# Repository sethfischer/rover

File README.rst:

=================
sethfischer/rover
=================

|build-status| |lint-status| |test-status| |docs-status| |linkcheck-status| |build-pcb-status|

Quarter-scale Mars rover based on the NASA Mars 2020 Mission Perseverance Rover.

Construction
------------

Refer to the `documentation <https://rover.fischer.nz/>`__.

Contribute
----------

Refer to `how to build a release`_ and follow the `additional steps for developers`_.

License
-------

:Software: SPDX-License-Identifier: MIT
:Hardware: SPDX-License-Identifier: CERN-OHL-W-2.0
:Documentation: SPDX-License-Identifier: CC-BY-NC-SA-4.0

.. _`how to build a release`: https://rover.fischer.nz/en/latest/build-release.html
.. _`additional steps for developers`: https://rover.fischer.nz/en/latest/build-release.html#additional-steps-for-developers

.. |build-status| image:: https://github.com/sethfischer/rover/actions/workflows/build.yml/badge.svg
    :target: https://github.com/sethfischer/rover/actions/workflows/build.yml
    :alt: Build status
.. |lint-status| image:: https://github.com/sethfischer/rover/actions/workflows/lint.yml/badge.svg
    :target: https://github.com/sethfischer/rover/actions/workflows/lint.yml
    :alt: Lint status
.. |test-status| image:: https://github.com/sethfischer/rover/actions/workflows/test.yml/badge.svg
    :target: https://github.com/sethfischer/rover/actions/workflows/test.yml
    :alt: Test status
.. |docs-status| image:: https://readthedocs.org/projects/sethfischer-osr/badge/?version=latest
    :target: https://sethfischer-osr.readthedocs.io/en/latest/?badge=latest
    :alt: Documentation Status
.. |linkcheck-status| image:: https://github.com/sethfischer/rover/actions/workflows/linkcheck.yml/badge.svg
    :target: https://github.com/sethfischer/rover/actions/workflows/linkcheck.yml
    :alt: Link Check Status
.. |build-pcb-status| image:: https://github.com/sethfischer/rover/actions/workflows/build-pcb.yml/badge.svg
    :target: https://github.com/sethfischer/rover/actions/workflows/build-pcb.yml
    :alt: PCB build status

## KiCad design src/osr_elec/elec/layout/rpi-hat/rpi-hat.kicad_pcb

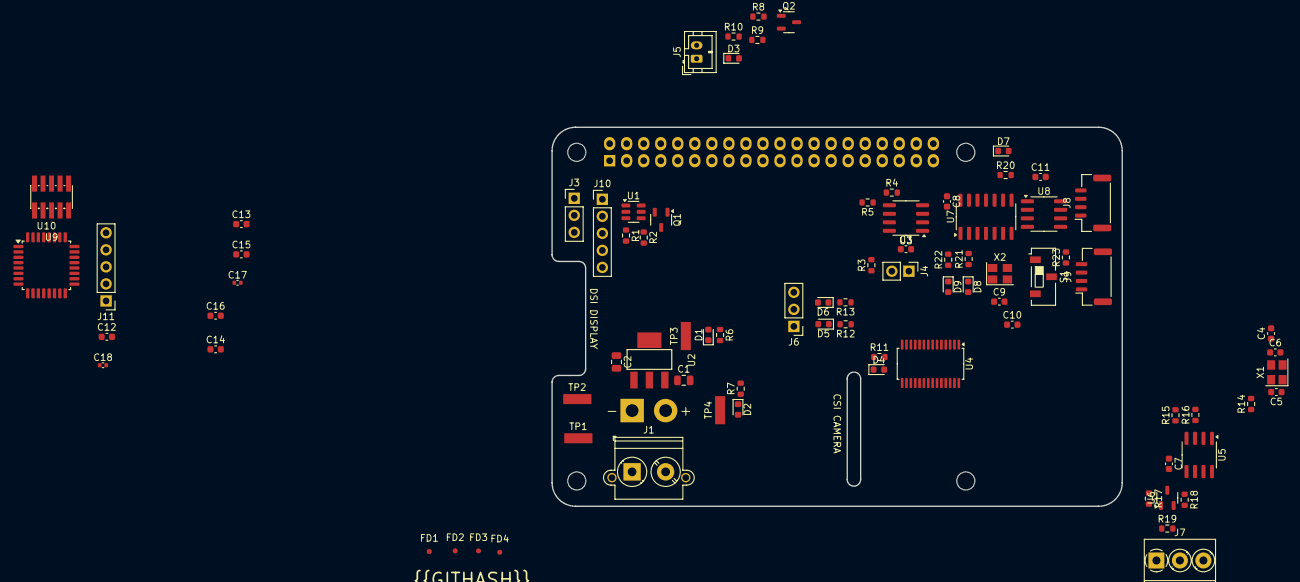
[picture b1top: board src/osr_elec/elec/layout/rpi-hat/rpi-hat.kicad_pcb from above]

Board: 4 copper layers, 85.0 x 56.5 mm, 88 parts (1 on the bottom side), 65 nets, no tracks yet.

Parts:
C1, C2: 25V 10uF X5R ±10% 0805 Multilayer Ceramic Capacit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; C0805
C3, C4, C7, C8, C11, C12, C13, C15: 50V 100nF X7R ±10% 0603 Multilayer Ceramic Capaci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; C0603
C5, C6, C9, C10: ?; C0603
C14, C16: 16V 4.7uF X5R ±10% 0603 Multilayer Ceramic Capaci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; C0603
C17: 50V 10nF X7R ±10% 0402 Multilayer Ceramic Capacit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; C0402
C18: 25V 1uF X5R ±10% 0402 Multilayer Ceramic Capacito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; C0402
D1, D2, D3, D4, D5, D6, D7, D8, D9: ?; LED_0603_1608Metric
FD1, FD2, FD3, FD4: ?; Fiducial_0.75mm_Mask1.5mm
J1: ?; Combo__AMASS_XT30PW-M_1x02_P2.50mm_Horizontal__TerminalBloc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
J2: ?; PinSocket_Samtec_ESQ-120-23-T-D_Oval_Pads
J3, J6: ?; PinHeader_1x03_P2.54mm_Vertical
J4: ?; PinHeader_1x02_P2.54mm_Vertical
J5: ?; JST_PH_B2B-PH-K_1x02_P2.00mm_Vertical
J7: ?; TerminalBlock_Phoenix_PT-1,5-3-3.5-H_1x03_P3.50mm_Horizontal
J8, J9: ?; JST_GH_SM04B-GHS-TB_1x04-1MP_P1.25mm_Horizontal
J10, J11: ?; PinHeader_1x05_P2.54mm_Vertical
Q1, Q2: ?; SOT-23-3
R1, R16: 100mW Thick Film Resistors 75V ±100ppm/℃ ±1% 10kΩ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; R0603
R2: 100mW Thick Film Resistors 75V ±100ppm/℃ ±1% 47kΩ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; R0603
R3: 100mW Thick Film Resistors 75V ±100ppm/℃ ±1% 1kΩ 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; R0603
R4, R5: 100mW Thick Film Resistors 75V ±100ppm/℃ ±1% 3.3k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; R0603
R6: 100mW Thick Film Resistors 75V ±100ppm/℃ ±1% 226Ω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; R0603
R7: 100mW Thick Film Resistors ±100ppm/℃ ±1% 487Ω 060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; R0603
R8: 100mW Thick Film Resistors 75V ±1% ±200ppm/℃ 100Ω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; R0603
R9: 100mW Thick Film Resistors 75V ±100ppm/℃ ±1% 1MΩ 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; R0603
R10: 100mW Thick Film Resistors 75V ±100ppm/℃ ±1% 402Ω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; R0603
R11, R20: 100mW Thin Film Resistor 75V ±25ppm/℃ ±0.1% 84.5Ω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; R0603
R12, R21: 100mW Thick Film Resistors 75V ±100ppm/℃ ±1% 330Ω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; R0603
R13, R22: 166.667mW Thin Film Resistor 75V ±0.5% ±25ppm/℃ 3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; R0603
R14, R15: 100mW Thick Film Resistors 75V ±100ppm/℃ ±1% 20Ω 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; R0603
R17, R18: 100mW Thick Film Resistors 75V ±1% ±400ppm/℃ 10Ω 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; R0603
R19, R23: 100mW Thick Film Resistors 75V ±100ppm/℃ ±1% 120Ω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; R0603
S1: ?; CK_JS102011JCQN_SW_SPDT_Slide_SMD
TP1, TP2, TP3, TP4: ?; Koa_Speer_RCWCTE_test_point
U1: ?; SOT-23-6
U2: ?; SOT-223-3_L6.5-W3.4-P2.30-LS7.0-BR
U3, U5, U8: ?; SOIC-8_3.9x4.9mm_P1.27mm
U4: ?; TSSOP-28_4.4x9.7mm_P0.65mm
U6: ?; SOT-23-3
U7: ?; SOIC-14_3.9x8.7mm_P1.27mm
U9: ?; HDR-SMD_10P-P1.27-V-M-R2-C5-LS5.3
U10: ?; LQFP-32_7x7mm_P0.8mm
X1, X2: ?; Crystal_SMD_Abracon_ABM8G-4Pin_3.2x2.5mm
_MH1, _MH2, _MH3, _MH4: MountingHole_2.7mm_M2.5_DIN965

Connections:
can_con_trx.can_leds.led_rx.resistor-cathode: D9.1, R22.1
can_con_trx.can_leds.led_tx.resistor-cathode: D8.1, R21.1
can_con_trx.controller-io: D7.2, U7.9
can_con_trx.controller-rx: R21.2, U7.2, U8.4
can_con_trx.controller-tx: R22.2, U7.1, U8.1
can_con_trx.controller-xin: C9.1, U7.6, X2.1
can_con_trx.controller-xout: C10.1, U7.5, X2.3
can_con_trx.switch-p1: R23.1, S1.1
can_con_trx.user_led_indicator.resistor-cathode: D7.1, R20.1
canh: J8.2, J9.2, S1.2, U8.7
canl: J8.3, J9.3, R23.2, U8.6
di: R15.1, U5.4
dsr_b: D4.2, U4.18
gate: Q2.1, R8.2, R9.1
gnd: C1.2, C2.2, C3.2, C4.2, C7.2, C8.2, C9.2, C10.2, C11.2, C12.2, C13.2, C14.2, C15.2, C16.2, C17.2, C18.2, J1.1, J2.6, J2.9, J2.14, J2.20, J2.25, J2.30, J2.34, J2.39, J3.1, J4.1, J6.1, J7.3, J8.4, J8.MP, J9.4, J9.MP, J10.1, Q2.2, R1.2, R2.2, R6.2, R7.2, R9.2, R11.2, R12.2, R13.2, R16.2, R20.2, TP1.1, TP2.1, U2.1, U3.1, U3.2, U3.3, U3.4, U4.9, U4.22, U5.5, U6.3, U7.7, U8.2, U9.3, U9.5, U9.9, U10.16, U10.31, U10.32, X2.2, X2.4
id_eeprom.wp_pullup-p1: J4.2, R3.1
ideal_diode-vcc: J2.2, J2.4, Q1.2, U1.5
mcu.jtag_header-reset: C12.1, U9.10, U10.4
miso: J2.35, U4.12, U7.12
mosi: J2.38, U4.11, U7.11
output_enable: R16.1, U5.2, U5.3
pa8: J11.1, U10.18
pa9: J11.2, U10.19
pa10: J11.3, U10.20
pa11: J11.4, U10.21
pa12: J11.5, U10.22
power_indicator_3v3.resistor-cathode: D1.1, R6.1
power_indicator_5v.resistor-cathode: D2.1, R7.1
q1_base: R1.1, U1.1, U1.2, U1.3
q2_collector: Q1.1, R2.1, U1.4
ro: R14.1, U5.1
robot_signal_light.status_indicator.resistor-cathode: D3.1, R10.1
robot_signal_light.switch.fet-gnd: J5.2, Q2.3, R10.2
rpi_header.connector-cs: J2.12, U4.10
rpi_header.connector-cs-1: J2.36, U7.13
rpi_header.connector-io: J2.7, J10.2
rpi_header.connector-io-1: J2.11, R8.1
rpi_header.connector-io-2: J2.26, U7.4
rpi_header.connector-rx: J2.10, J3.3
rpi_header.connector-scl: J2.3, J10.3, U10.29
rpi_header.connector-scl-1: J2.28, R5.1, U3.6
rpi_header.connector-sda: J2.5, J10.4, U10.30
rpi_header.connector-sda-1: J2.27, R4.1, U3.5
rpi_header.connector-tx: J2.8, J3.2
rpi_header.connector-vcc: J2.1, J2.17
rs485_trx.series_resistors-a: J7.1, R17.2, R19.1, U6.1
rs485_trx.series_resistors-b: J7.2, R18.2, R19.2, U6.2
rs485_trx.trx-a: R17.1, U5.6
rs485_trx.trx-b: R18.1, U5.7
sck: J2.40, U4.13, U7.10
tck: U9.4, U10.24
tms: U9.2, U10.23
uart_converter-rx: D6.2, J6.3, U4.4
uart_converter-rx-1: R14.2, U4.24
uart_converter-tx: D5.2, J6.2, U4.3
uart_converter-tx-1: R15.2, U4.23
uart_converter.converter-xin: C5.1, U4.6, X1.1
uart_converter.converter-xout: C6.1, U4.7, X1.3
uart_converter.converter_osc-gnd: C5.2, C6.2, X1.2, X1.4
uart_converter.user_led_indicator.resistor-cathode: D4.1, R11.1
uart_leds.led_rx.resistor-cathode: D6.1, R13.1
uart_leds.led_tx.resistor-cathode: D5.1, R12.1
vcc-3v3: C2.1, C3.1, C4.1, C7.1, C8.1, C11.1, C13.1, C14.1, C15.1, C16.1, C17.1, C18.1, D1.2, D8.2, D9.2, J8.1, J9.1, J10.5, R4.2, R5.2, TP3.1, U2.2, U2.4, U3.8, U4.8, U5.8, U7.14, U8.3, U9.1, U10.1, U10.5, U10.17
vcc-5v: C1.1, D2.2, D3.2, J1.2, J5.1, Q1.3, TP4.1, U1.6, U2.3
wp: R3.2, U3.7

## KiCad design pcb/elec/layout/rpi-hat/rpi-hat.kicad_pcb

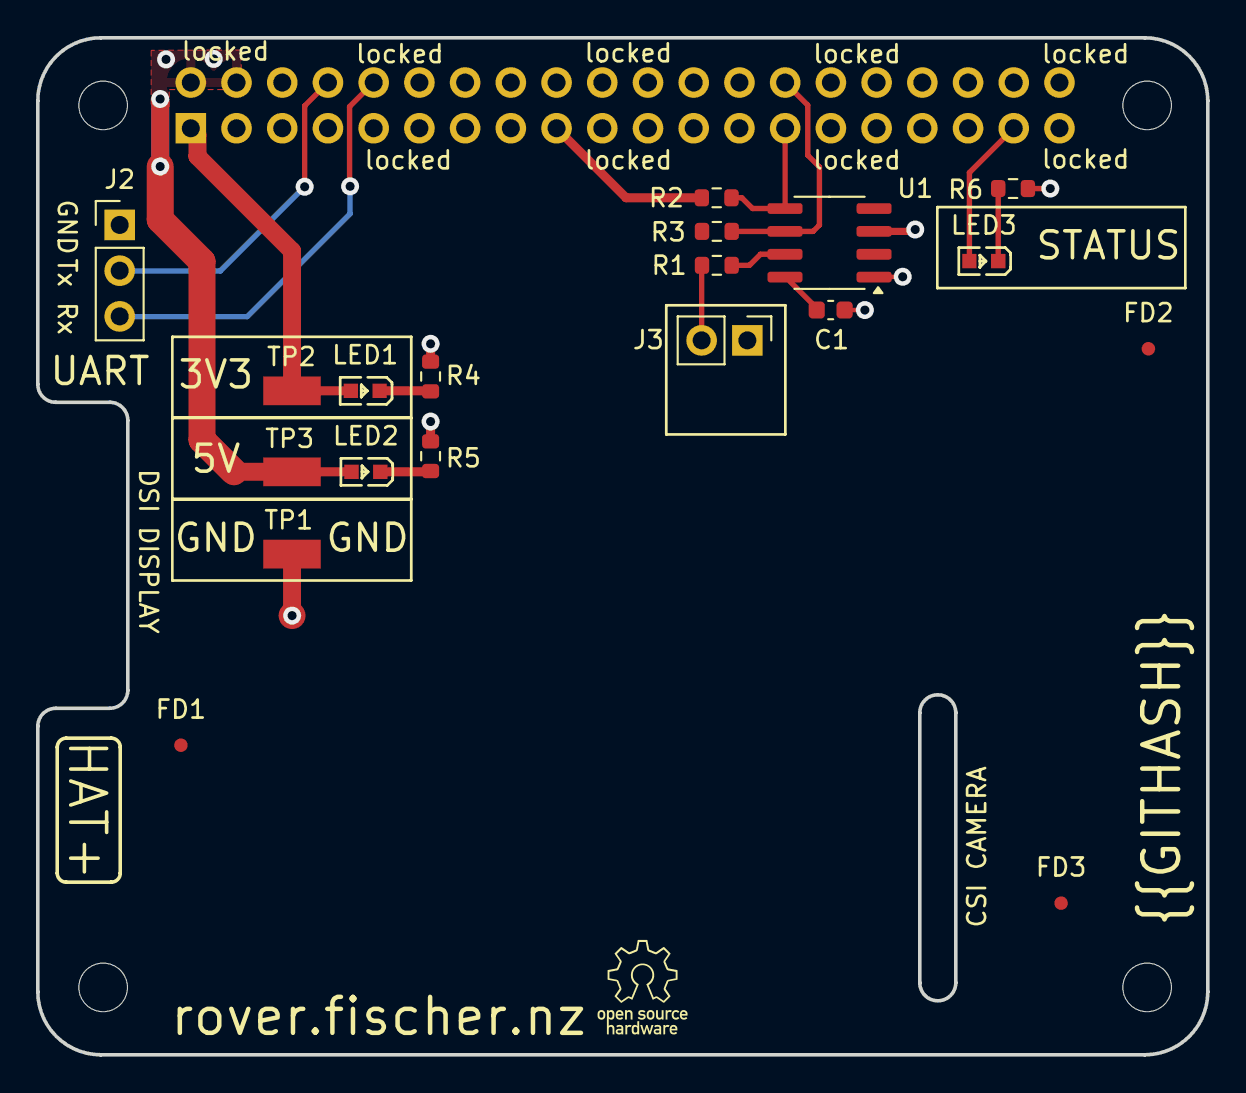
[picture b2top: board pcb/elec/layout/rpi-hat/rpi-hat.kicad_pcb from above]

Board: 2 copper layers, 65.0 x 56.5 mm, 26 parts (1 on the bottom side), 13 nets.

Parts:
C1: 50V 100nF X7R ±10% 0603 Multilayer Ceramic Capaci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; C0603
FD1, FD2, FD3: Fiducial_0.75mm_Mask1.5mm
GL1: Logo_RPi_Hat_Plus_Wordmark_3.5mm_SilkscreenTop
GL2: Logo_OSHW_5mm_SilkscreenTop
J1: PinSocket_2x20_P2.54mm_Vertical
J2: PinHeader_1x03_P2.54mm_Vertical
J3: PinHeader_1x02_P2.54mm_Vertical
LED1, LED2, LED3: LED0603-RD
R1: 100mW Thick Film Resistors 75V ±100ppm/℃ ±1% 1kΩ 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; R0603
R2, R3: 100mW Thick Film Resistors ±100ppm/℃ ±1% 3.9kΩ 06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; R0603
R4: 100mW Thick Film Resistors ±100ppm/℃ ±1% 226Ω 060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; R0603
R5: 100mW Thick Film Resistors ±100ppm/℃ ±1% 487Ω 060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; R0603
R6: 100mW Thin Film Resistor ±25ppm/℃ ±1% 549Ω 0603 C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; R0603
TP1, TP2, TP3: Koa_Speer_RCWCTE_test_point
U1: SOIC-8_3.9x4.9mm_P1.27mm
_MH1, _MH2, _MH3, _MH4: MountingHole_2.7mm

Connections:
gnd: C1.2, J1.6, J1.9, J1.14, J1.20, J1.25, J1.30, J1.34, J1.39, J2.1, J3.1, R4.2, R5.2, R6.2, TP1.1, U1.1, U1.2, U1.3, U1.4
gpio26: J1.37, LED3.2
p1: J3.2, R1.1
power_indicator_3v3.resistor-cathode: LED1.1, R4.1
power_indicator_5v.resistor-cathode: LED2.1, R5.1
rpi_header-scl-1: J1.28, R3.1, U1.6
rpi_header-sda-1: J1.27, R2.1, U1.5
rx: J1.10, J2.3
status_indicator_robot.resistor-cathode: LED3.1, R6.1
tx: J1.8, J2.2
vcc: C1.1, J1.1, J1.17, LED1.2, R2.2, R3.2, TP2.1, U1.8
vcc-1: J1.2, J1.4, LED2.2, TP3.1
wp: R1.2, U1.7

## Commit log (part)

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2022-09-04 build: update docs requirements
    Update due to change in format introduced by Poetry 1.2.0.
2022-09-05 feat: frame assembly
2022-09-06 refactor: implement class point2d
2022-09-06 refactor: read point2d values by name
2022-09-07 refactor: correctly reference class constants
2022-09-08 refactor: implement cq abstract base classes
2022-09-11 test: frame assembly and jigs
2022-09-11 test: aec 20 series v-slot extrusion
2022-09-11 test: aec 20-series bore slot sketch
2022-09-17 feat: rocker axle assembly
2022-09-18 build: update dependencies
2022-09-22 feat: export image of final assembly
2022-09-25 build: command to create open graph image
2022-09-25 build: update key words
2022-09-25 refactor: consistent naming
2022-09-25 refactor: consistent variable names
2022-09-26 docs: how to build a release
2022-09-26 build: include changelog in release
2022-09-26 fix: create venv with correct python version
2022-09-26 refactor: improve structure
2022-09-27 build: create release readme file
2022-09-27 docs: improved headings
2022-09-27 refactor: use config in open graph svg
2022-09-28 refactor: move long description to config
2022-09-28 fix: readme links
2022-09-28 refactor: move copyright notice to config
2022-09-28 build: poetry group cq-editor
2022-09-29 build: upgrade cq_warehouse
2022-09-30 build: create release archives
2022-10-01 refactor: replace invoke with subprocess
2022-10-01 refactor: import only used elements
2022-10-01 build: remove invoke mypy overrides
2022-10-09 feat: control electronics din rail and rpi
2022-10-09 refactor: mark make methods for internal use
2022-10-09 refactor: namespace assembly names
2022-10-09 build: fix out-of-date final assembly image
2022-10-09 build: optimise open graph image
2022-10-09 build: optimise exported png image
2022-10-09 docs: install optipng
2022-10-10 refactor: fix shadow of built-in name
2022-10-11 refactor: 2020 end tap jig
2022-10-11 build: use built-in collection types
2022-10-14 refactor: open graph card templates
2022-10-15 refactor: use cairosvg to render open graph card
2022-10-15 docs: improved parameter description
2022-10-15 test: alexco 2020 profile
2022-10-24 refactor: rocker axle assembly
2022-10-30 refactor: subclass control electronics
2022-11-04 feat: generate bill of materials
2022-11-05 build: git-lfs with rtd build process
2022-11-05 refactor: build release
2022-11-05 refactor: frame assembly names
2022-11-05 refactor: frame bom parts
2022-11-18 refactor: frame sub-assemblies
2022-11-18 refactor: remove call to deprecated method
2022-11-19 refactor: parts method name
2022-11-19 refactor: decouple base classes
2022-11-19 build: improve typing coverage
2022-11-20 refactor: rename post -> pillar
2022-11-20 fix: rocker axle location
2022-11-22 refactor: cq base classes
2022-11-23 refactor: generate assembly names
2022-11-23 refactor: rename axle_support -> axle_pillar
2022-11-26 fix: remove stdout info generated by export
2022-12-01 refactor: improve typing coverage
2022-12-01 refactor: export wrapper exception on stderr
2022-12-02 refactor: improve part identifier class
2022-12-02 refactor: store part quantity by assembly
2022-12-03 build: update pytest to 7.2.0
2022-12-03 build: update mypy to 0.991
2022-12-03 build: update sphinx to 5.3.0
2022-12-03 build: update dev dependencies
2022-12-03 docs: spelling corrections
2022-12-03 build: update git-lfs to 3.3.0
2022-12-06 build: update cadquery to 2.2.0b2
2022-12-08 build: remove poetry-core version
2022-12-08 build: consistent docstrings
2022-12-09 ci: fix workflow job name
2022-12-09 docs: bill of materials
2022-12-10 refactor: del unused variables
2022-12-10 refactor: correct variable names
2022-12-10 style: white-space changes
2022-12-10 build: spelling correction
2022-12-11 style: remove white-space in inline tables
2022-12-13 style: remove unused namespace from svg
2022-12-13 refactor: remove parameter used for solely test
2022-12-14 refactor: move common utilities into own package
2022-12-14 test: refactor v-slot tests
2022-12-14 test: refactor to use cq public api
2022-12-14 test: stricter type detection
2022-12-14 test: fix shf8 shaft support test
2022-12-15 refactor: stricter typing for cq containers
2022-12-15 ci: enable mypy strict mode
2022-12-16 build: type profile as cq sketch
2022-12-17 refactor: simple is keyword-only argument
2022-12-17 refactor: make cq export wrapper callable
2022-12-17 refactor: make fastener to part converter callable
2023-01-04 docs: bump copyright year
2023-01-10 docs: vtk render of main assembly and end-tap jig
2023-01-15 ci: upgrade github actions versions
2023-01-15 build: editor trim trailing whitespace
2023-01-15 style: format pyproject.toml
2023-01-15 build: install rtd dependencies with poetry
2023-01-21 build: update sphinxcontrib-cadquery to 0.3.0
2023-01-22 docs: refactor outline
2023-01-22 docs: add index entries
2023-01-22 docs: render frame assembly
2023-01-22 docs: show headings in toctree
2023-01-22 docs: add indices to side navigation
2023-01-22 docs: 3d print settings directive
2023-01-22 docs: 2020 end tap jig bom
2023-01-23 docs: render 2020 end-tap jig body
2023-01-23 docs: render frame sides
2023-01-24 docs: frame side boms
2023-01-25 refactor: osr sphinx domain
2023-01-29 build: update sphinxcontrib-cadquery to 0.4.0
2023-02-03 build: validate print settings nozzle, layer
2023-02-04 build: update cadquery to 2.2.0
2023-02-04 build: update cq-electronics
2023-02-04 build: add py.typed to osr_common module
2023-02-06 build: multilayer dxf builder utility
2023-02-06 refactor: move multilayer dxf class to osr_common
2023-02-06 refactor: move cq_wrappers to osr_common
2023-02-06 refactor: rename dxf exporter
2023-02-06 build: add metadata parameter to dxf exporter
2023-02-06 refactor: dxf exporter metadata default
2023-02-08 refactor: add param setup to dxf builder
2023-02-11 refactor: dxf exporter
    * init params to match ezdxf
    * imporved typing
    * improve doc strings
2023-02-14 docs: inspiration section
2023-02-16 docs: add dimensions calculated from model
2023-02-17 docs: fix perseverance model width on mobile
2023-02-17 docs: hide toc and add indices section
2023-02-24 docs: competitions section
2023-03-03 build: poetry disable modern installation
    Disable modern Poetry installation due to:
    AssertionError
    In cadquery_ocp-7.7.0a0-cp39-cp39-manylinux_2_31_x86_64.whl,
    LICENSES_bundled.txt is not mentioned in RECORD
    Modern installation was introduced with Poetry 1.4.0
2023-03-03 docs: fix dimension order
2023-03-05 build: update sphinxcontrib-cadquery to 0.5.0
2023-03-05 docs: add arc and iprc to competitions section
2023-03-25 docs: end-tap jig print orientation
2023-04-07 docs: tech promotion grid
2023-04-08 docs: link to github repo in header
2023-04-08 docs: frame sub assembly toc heading
2023-04-08 docs: add target for technology section
2023-04-09 docs: din rail assemblies
2023-04-09 docs: rocker axle section
2023-04-09 chore: remove duplicate conf variable
2023-04-10 chore: change project name to "sethfischer-rover"
2023-04-10 docs: add exiftool to build prerequisites
2023-04-21 docs: site icon
2023-04-22 docs: add sections copyright and about
2023-05-12 docs: update project description
2023-05-15 docs: add open graph image
2023-05-15 docs: improve meta descriptions
2023-05-16 docs: improve html page title
2023-05-16 docs: update index page title
2023-05-16 docs: update build release instructions
2023-05-17 chore: update dependencies
2023-05-17 chore: update mypy to 1.3.0
2023-05-17 chore: update cairosvg to 2.7.0
2023-05-26 docs: add lego technic rover to related projects
2023-06-28 docs: add captions to figures
2023-10-24 chore: bump pillow 9.5.0 -> 10.1.0
2023-10-24 chore: bump sphinx-design 0.4.1 -> 0.5.0
2023-12-01 docs: add geek club rover to related projects
2023-12-02 docs: update nasa-jpl website url
2023-12-02 test: periodic link check
2023-12-02 docs: update git-lfs url
2023-12-02 test: fix linkcheck workflow
2023-12-03 docs: remove sphero littlebits from related projects
    The Sphero LittleBits Space Rover Inventor Kit has been discontinued.
2023-12-05 test: configure linkcheck_allowed_redirects
2024-01-10 docs: link to documentation site
2024-01-10 chore: configure flake8-bugbear
2024-02-15 chore: bump cadquery 2.3.1 -> 2.4.0
2024-02-16 docs: generate changelog
2024-02-16 chore: set mwg image tags
2024-02-17 chore: require python 3.11
2024-02-17 refactor: make open graph card
2024-02-17 style: ignore pylint message w0212
2024-02-17 style: consistent single quotes
2024-02-19 style: prefix unused variable with underscore
2024-02-20 style: remove unused future imports
2024-02-21 refactor: point2d namedtuple
2024-02-22 ci: upgrade github actions/checkout 3 -> 4
2024-02-23 chore: fix cq-editor dependency resolution
2024-02-23 chore: downgrade pyqtgraph to ^0.12.4
2024-02-29 build: fix rtd build for poetry 1.8
2024-02-29 feat: command to generate rpi hat outline
2024-03-05 fix: rpi hat pcb outline
    Export only the face of the board as DXF.
2024-03-11 fix: exclude mounting holes from rpi hat outline
2024-03-11 fix: rpi pcb outline fillet
2024-03-25 feat: rpi hat pcb
2024-04-19 build: pinout sphinx extension
2024-04-19 docs: vmc pinout diagram
2024-06-11 docs: remove nasa-jpl 3d model
2024-06-17 docs: vmc daughter board directed graph
2024-06-21 feat: vmc daughter pcb
    Vehicle Management Computer daughter PCB.
2024-06-21 refactor: pin header 1x2 from headers package
2024-06-21 refactor: pin header 1x3 from headers package
2024-06-21 refactor: pin header 1x5 from headers package
2024-06-21 refactor: rpi gpoi header footprint from headers package
2024-06-21 chore: remove unused 3d model pin header 2x20
2024-06-21 refactor: rename can termination switch 3d model
2024-06-22 chore: update footprints
2024-06-23 refactor: can termination switch from ck-js-series package
2024-06-27 refactor: terminal block from package phoenix-pt-series
2024-06-28 chore: update footprint lib descriptions
2024-06-28 chore: remove pcb mech/ directory
2024-07-02 refactor: use kicad global libs for terminal block
2024-07-02 fix: remove make mech files
2024-07-10 chore: update black 24.2.0 -> 24.4.2
2024-07-10 chore: update mypy 1.8.0 -> 1.10.1
2024-07-10 chore: update pillow 10.2.0 -> 10.4.0
2024-07-11 chore: update dependencies
    Update dependencies:
    * certifi (2024.2.2 -> 2024.7.4)
    * idna (3.6 -> 3.7)
    * typing-extensions (4.9.0 -> 4.12.2)
    * urllib3 (2.2.1 -> 2.2.2)
    * annotated-types (0.6.0 -> 0.7.0)
2024-07-11 docs: update perseverance links
2024-07-11 docs: rename section vmc interfaces -> datasheet
2024-07-12 style: white space correction
2024-07-14 feat: rpi hat outline full width
2024-07-26 ci: define canonical url and context for rtd
2024-08-02 docs: add redirect file to release archive
2024-08-02 chore: rpi hat electronic design
2024-08-02 chore: install atopile
2024-08-02 chore: rpi hat+ symbol footprint
2024-08-02 chore: atopile project scaffolding
2024-08-02 wip: layout
2024-08-02 ci: build pcbs
2024-11-14 chore: update dependencies
    - certifi (2024.7.4 -> 2024.8.30)
    - charset-normalizer (3.3.2 -> 3.4.0)
    - idna (3.7 -> 3.10)
    - markupsafe (2.1.5 -> 3.0.2)
    - urllib3 (2.2.2 -> 2.2.3)
    - babel (2.15.0 -> 2.16.0)
2024-11-14 chore: update sphinx-design 0.5.0 -> 0.6.1
2024-11-23 chore: update sphinx 6.2.1 -> 7.4.7
2024-11-23 chore: update pillow 10.4.0 -> 11.0.0
2024-12-04 chore: update commitizen 3.31.0 -> 4.0.0
2024-12-05 chore: exclude lego.com from linkcheck
2024-12-06 chore: allow imagemagick redirect
2025-01-27 chore: exclude 4tronix links from linkcheck
2025-01-31 docs: update link to bricolabs project
2025-02-21 ci: run linkcheck on push
2025-03-22 chore: exclude esa.int from linkcheck
2025-07-22 build: upgrade to python 3.12
2025-07-22 ci: remove push action link check
2025-07-22 chore: update linkcheck ignore list
2025-07-23 chore: document github token
2025-07-23 docs: add sunfounder galaxyrvr to related projects
2025-07-23 docs: group self-build projects into section

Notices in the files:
pcb/elec/layout/rpi-hat/rpi-hat.kicad_pcb:
© 2024 Seth Fischer
